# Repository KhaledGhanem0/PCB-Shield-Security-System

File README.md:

# Custom PCB Shield for Multi-Zone Security System

A custom two-layer **Arduino Mega** shield PCB designed to replace the breadboard prototype of the Multi-Zone Smart Security System. The board consolidates all control and sensing connections into a single, permanent, and reliable hardware platform.

> 🔗 **Firmware Repository:** [Multi-Zone Smart Security System](https://github.com/KhaledGhanem0/Smart-Security-System)

---

## Table of Contents

- [Overview](#overview)
- [Schematic](#schematic)
- [PCB Layout](#pcb-layout)
- [3D Render](#3d-render)
- [Design Specifications](#design-specifications)
- [Bill of Materials](#bill-of-materials)
- [File Structure](#file-structure)
- [License](#license)

---

## Overview

This project is a direct continuation of the [Multi-Zone Smart Security System](https://github.com/KhaledGhanem0/Smart-Security-System). The breadboard prototype, while functional, was not a reliable or permanent form factor. This shield was designed in **KiCad** to produce a clean, manufacturable PCB that sits directly on top of the Arduino Mega 2560 and exposes all the necessary connectors for the system's peripherals.

The design follows standard Arduino shield dimensions, ensuring mechanical compatibility with the Mega footprint. All components are through-hole (THT), making the board straightforward to solder by hand. The schematic was drawn as a single sheet with clear net labeling, and the PCB layout was routed with dedicated power and signal trace widths, a ground copper pour on the back copper layer, and a defined keep-out zone to avoid interference with the Arduino's onboard components.

---

## Schematic

The schematic captures the complete connectivity of all shield components in a single sheet. Each peripheral is connected to the appropriate Arduino Mega pins, with net labels used throughout to keep the diagram readable and avoid long crossing wires.

Key connections documented in the schematic:

- **RFID Reader (MFRC522)** — SPI bus (MOSI, MISO, SCK) with a dedicated chip-select pin
- **ESP8266 Wi-Fi Module** — Serial1 hardware UART (TX1 / RX1, pins 18–19)
- **LCD Screen** — 4-bit parallel interface
- **4×4 Keypad** — 8 digital I/O pins (4 rows, 4 columns)
- **PIR Sensors & Reed Switches** — Digital input pins, one per sensor across all three zones
- **Buzzers** — Digital output pins, one per zone
- **Power distribution** — 5 V and 3.3 V rails routed from the Arduino's onboard regulators to the appropriate peripherals

---

## PCB Layout

The PCB is sized to match Arduino Mega shield dimensions, with connectors positioned to align with the Mega's header rows. Components are placed on the front side only (all THT). A keep-out zone is defined over the Arduino's onboard USB and power jack area to prevent clearance violations.

Routing highlights:

- Signal traces routed at **0.25 mm** width
- Power traces routed at **0.5 mm** width
- **12 vias** used to transition signals between layers where needed
- **Ground copper pour** applied to the full B.Cu (back copper) layer, connected to the GND net
- All 5 V connections made through dedicated routed tracks on F.Cu

---

## 3D Render

The images below show the KiCad 3D render of the board before fabrication. All component footprints are placed on the front side of the board.

**Front**

**Back**

---

## Design Specifications

### Board Stackup

| Layer | Type | Thickness | Material |
|---|---|---|---|
| F.Silkscreen | Top Silk Screen | — | — |
| F.Paste | Top Solder Paste | — | — |
| F.Mask | Top Solder Mask | 0.01 mm | — |
| F.Cu | Copper | 0.035 mm | — |
| Dielectric 1 | Core | 1.51 mm | FR4 |
| B.Cu | Copper | 0.035 mm | — |
| B.Mask | Bottom Solder Mask | 0.01 mm | — |
| B.Paste | Bottom Solder Paste | — | — |
| B.Silkscreen | Bottom Silk Screen | — | — |

**Total board thickness:** 1.6 mm | **Solder mask color:** Green

### Board Dimensions

| Property | Value |
|---|---|
| Width | 100.584 mm |
| Height | 78.232 mm |
| Area | 7,863 mm² |

### Routing Rules

| Parameter | Value |
|---|---|
| Signal trace width | 0.25 mm |
| Power trace width | 0.50 mm |
| Minimum clearance | 0.2 mm |
| Copper to edge clearance | 0.075 mm |
| Minimum via diameter | 0.4 mm |
| Minimum drill (through hole) | 0.3 mm |
| Hole to hole clearance | 0.25 mm |

### Board Statistics

| Item | Count |
|---|---|
| THT components | 27 |
| Through-hole pads | 170 |
| NPTH (mounting holes) | 6 |
| Through vias | 12 |
| Total components | 33 |

---

## Bill of Materials

> The table below lists the components used on the shield.

| Reference | Value / Description | Footprint | Qty |
|---|---|---|---|
| DS1 | WC1602A (LCD Screen) | IDC Header 2×8, 2.54 mm | 1 |
| J1 | Power Header | Pin Header 1×8, 2.54 mm | 1 |
| J2 | PWM Header | Pin Header 1×10, 2.54 mm | 1 |
| J3, J5 | Analog Headers | Pin Header 1×8, 2.54 mm | 2 |
| J4 | PWM Header | Pin Header 1×8, 2.54 mm | 1 |
| J6 | Communication Header | Pin Header 1×8, 2.54 mm | 1 |
| J7 | Digital Header | Pin Header 2×18, 2.54 mm | 1 |
| J8 | ESP-01 (ESP8266 Wi-Fi Module) | ESP-01 Module Footprint | 1 |
| J9, J10 | Connectors 1×8 | Pin Header 1×8, 2.54 mm | 2 |
| J11, J13, J14 | Screw Terminal 3-pin (PIR Sensors) | Phoenix PT 1×3, 5.0 mm | 3 |
| J12, J15, J16, J17, J18, J19 | Screw Terminal 2-pin (Reed Switches) | Phoenix PT 1×2, 5.0 mm | 6 |
| J20, J21 | Socket Connectors 1×6 | Pin Socket 1×6, 2.54 mm | 2 |
| D1, D2, D3 | LED 5 mm (Zone Alarms) | LED THT, D5.0 mm | 3 |
| R1 | Resistor 220 Ω | Axial DIN0207, 7.62 mm pitch | 1 |
| RV1 | Potentiometer (LCD Contrast) | Bourns 3386P Vertical | 1 |

---

## File Structure

```
├── kicad/
│   ├── Security System Arduino Shield.kicad_pro   # KiCad project file
│   ├── Security System Arduino Shield.kicad_sch   # Schematic
│   ├── Security System Arduino Shield.kicad_pcb   # PCB layout
│   └── fp-lib-table                               # Footprint library references
├── images/
│   ├── schematic.pdf                              # Schematic PDF
│   ├── pcb_layout.png                             # PCB layout screenshot
│   ├── 3d_front.png                               # 3D render, front side
│   └── 3d_back.png                                # 3D render, back side
├── LICENSE
└── README.md
```

---

## License

This project is licensed under the [MIT License](LICENSE).

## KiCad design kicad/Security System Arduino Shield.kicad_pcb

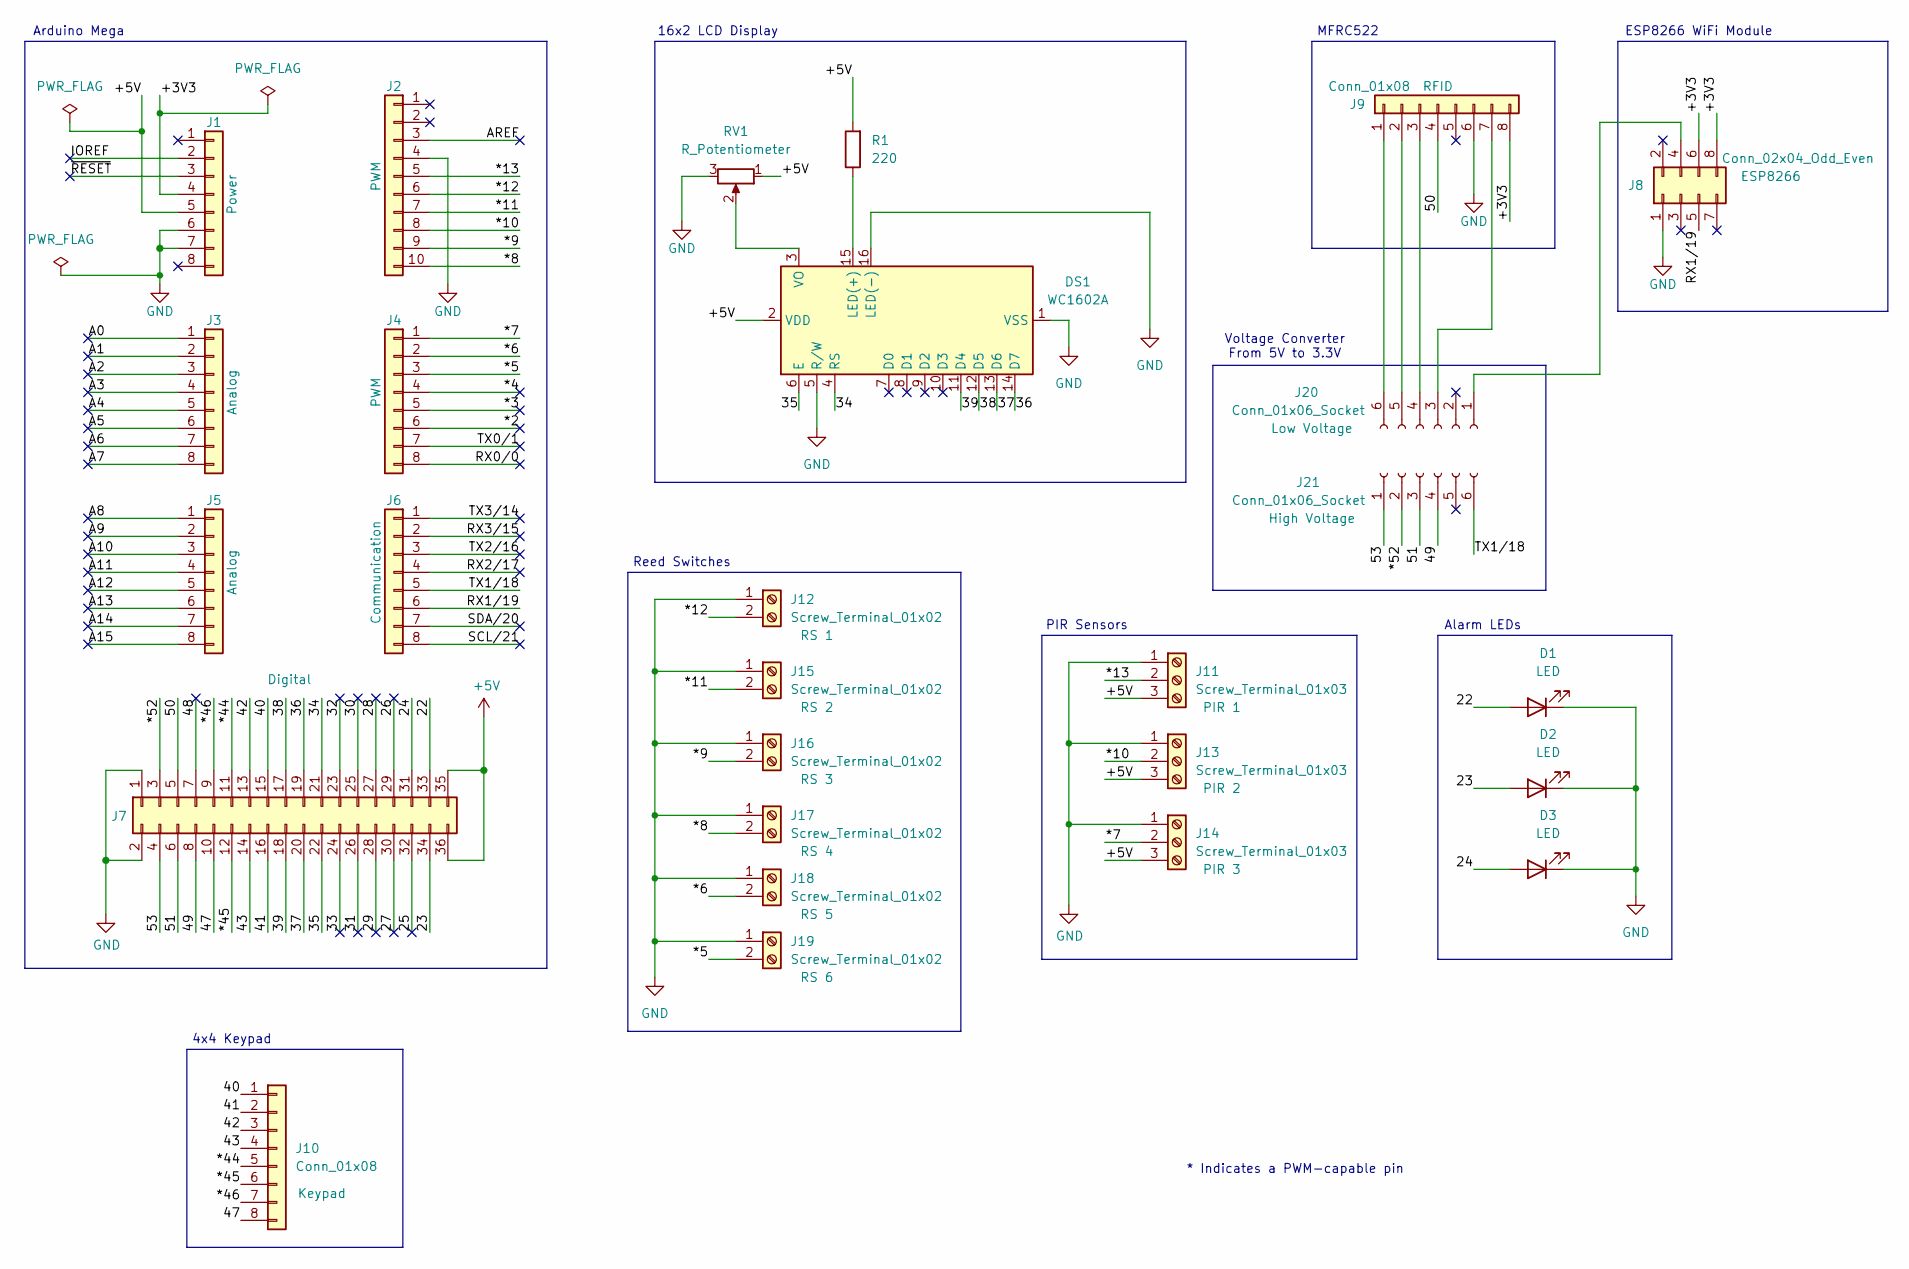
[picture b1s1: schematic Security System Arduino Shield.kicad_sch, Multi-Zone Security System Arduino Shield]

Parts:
D1, D2, D3: LED; LED_D5.0mm
DS1: WC1602A; IDC-Header_2x08_P2.54mm_Vertical
J1: Power; PinHeader_1x08_P2.54mm_Vertical
J2: PWM; PinHeader_1x10_P2.54mm_Vertical
J3, J5: Analog; PinHeader_1x08_P2.54mm_Vertical
J4: PWM; PinHeader_1x08_P2.54mm_Vertical
J6: Communication; PinHeader_1x08_P2.54mm_Vertical
J7: Digital; PinHeader_2x18_P2.54mm_Vertical
J8: Conn_02x04_Odd_Even; ESP-01
J9, J10: Conn_01x08; PinHeader_1x08_P2.54mm_Vertical
J11, J13, J14: Screw_Terminal_01x03; TerminalBlock_Phoenix_PT-1,5-3-5.0-H_1x03_P5.00mm_Horizontal
J12, J15, J16, J17, J18, J19: Screw_Terminal_01x02; TerminalBlock_Phoenix_PT-1,5-2-5.0-H_1x02_P5.00mm_Horizontal
J20, J21: Conn_01x06_Socket; PinSocket_1x06_P2.54mm_Vertical
R1: 220; R_Axial_DIN0207_L6.3mm_D2.5mm_P7.62mm_Horizontal
RV1: R_Potentiometer; Potentiometer_Bourns_3386P_Vertical

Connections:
+5V: DS1.2 (VDD), J1.5, J7.35, J7.36, J11.3, J13.3, J14.3, R1.2, RV1.1
/22: D1.2 (A), J7.33
/23: D2.2 (A), J7.34
/24: D3.2 (A), J7.31
/25: J7.32
/26: J7.29
/27: J7.30
/28: J7.27
/29: J7.28
/30: J7.25
/31: J7.26
/32: J7.23
/33: J7.24
/34: DS1.4 (RS), J7.21
/35: DS1.6 (E), J7.22
/36: DS1.14 (D7), J7.19
/37: DS1.13 (D6), J7.20
/38: DS1.12 (D5), J7.17
/39: DS1.11 (D4), J7.18
/40: J7.15, J10.1
/41: J7.16, J10.2
/42: J7.13, J10.3
/43: J7.14, J10.4
/47: J7.10, J10.8
/48: J7.7
/49: J7.8, J21.4
/50: J7.5, J9.4
/51: J7.6, J21.3
/53: J7.4, J21.1
/*2: J4.6
/*3: J4.5
/*4: J4.4
/*5: J4.3, J19.2
/*6: J4.2, J18.2
/*7: J4.1, J14.2
/*8: J2.10, J17.2
/*9: J2.9, J16.2
/*10: J2.8, J13.2
/*11: J2.7, J15.2
/*12: J2.6, J12.2
/*13: J2.5, J11.2
/*44: J7.11, J10.5
/*45: J7.12, J10.6
/*46: J7.9, J10.7
/*52: J7.3, J21.2
/+3V3: J1.4, J8.6, J8.8, J9.8
/A0: J3.1
/A1: J3.2
/A2: J3.3
/A3: J3.4
/A4: J3.5
/A5: J3.6
/A6: J3.7
/A7: J3.8
/A8: J5.1
/A9: J5.2
/A10: J5.3
/A11: J5.4
/A12: J5.5
/A13: J5.6
/A14: J5.7
/A15: J5.8
/AREF: J2.3
/IOREF: J1.2
/RX0/0: J4.8
/RX1/19: J6.6, J8.5
/RX2/17: J6.4
/RX3/15: J6.2
/SCL/21: J6.8
/SDA/20: J6.7
/TX0/1: J4.7
/TX1/18: J6.5, J21.6
/TX2/16: J6.3
/TX3/14: J6.1
/~RESET: J1.3
GND: D1.1 (K), D2.1 (K), D3.1 (K), DS1.1 (VSS), DS1.5 (R/W), DS1.16 (LED(-)), J1.6, J1.7, J2.4, J7.1, J7.2, J8.1, J9.6, J11.1, J12.1, J13.1, J14.1, J15.1, J16.1, J17.1, J18.1, J19.1, RV1.3
unnamed: DS1.15 (LED(+)), R1.1
unnamed: DS1.3 (VO), RV1.2
unnamed: J8.4, J20.1
unnamed: J9.7, J20.3
unnamed: J9.3, J20.4
unnamed: J9.2, J20.5
unnamed: J9.1, J20.6

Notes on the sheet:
Alarm LEDs
PIR Sensors
MFRC522
Arduino Mega
Voltage Converter From 5V to 3.3V
* Indicates a PWM-capable pin
ESP8266 WiFi Module
Reed Switches
4x4 Keypad
16x2 LCD Display

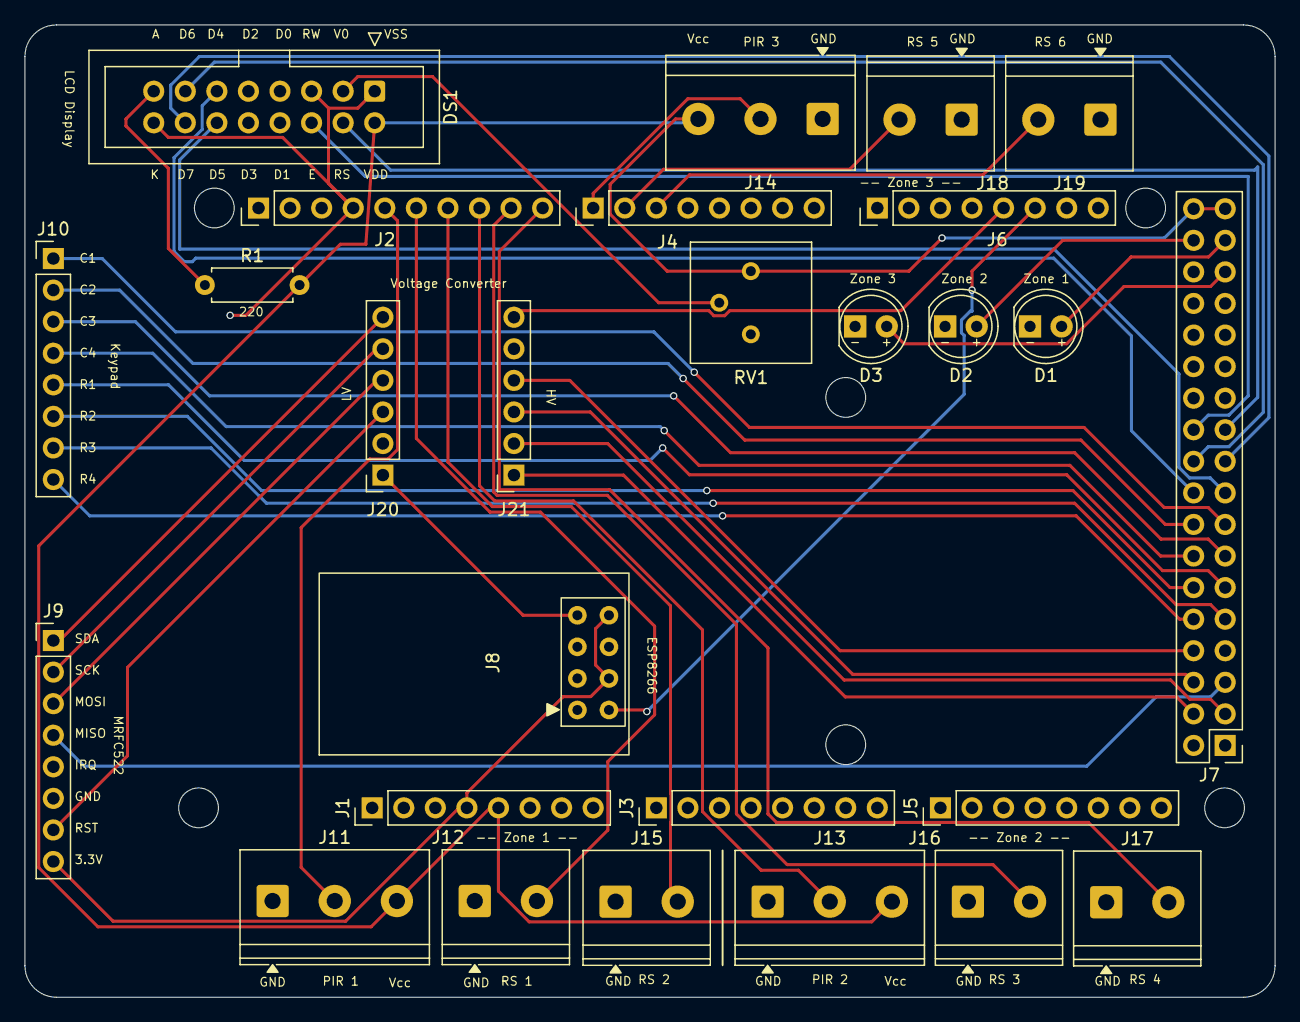
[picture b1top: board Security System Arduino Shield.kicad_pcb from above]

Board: 2 copper layers, 100.6 x 78.2 mm, 33 parts (0 on the bottom side), 43 nets.

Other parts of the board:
MH1, MH2, MH3, MH4, MH5, MH6: MountingHole_3.2mm

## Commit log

2026-05-18 Rename pcb_layout.png to images/pcb_layout.png
2026-05-18 Rename Security System Arduino Shield.kicad_pro to kicad/Security System Arduino Shield.kicad_pro
2026-05-18 Rename 3d_layout.png to 3d_front.png

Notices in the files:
README.md:
License: MIT
